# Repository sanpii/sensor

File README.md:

Temperature/humidity sensor over mqtt.

This is a part of [Uncontrolled Mechanical
Ventilation](https://hackaday.io/project/12708-uncontrolled-mechanical-ventilation)
project.

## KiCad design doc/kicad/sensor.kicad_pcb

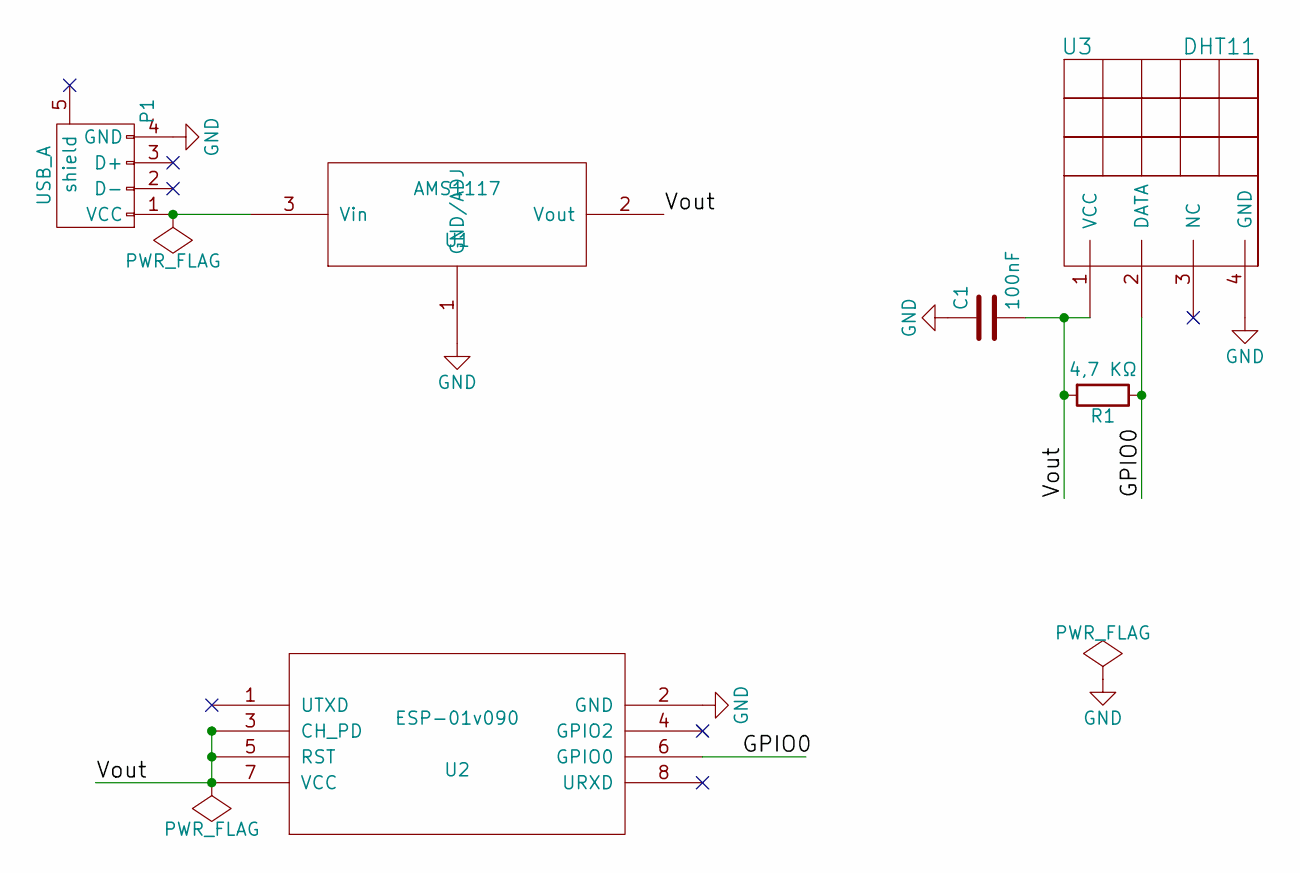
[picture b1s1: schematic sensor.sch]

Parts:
C1: 100nF; C_Disc_D3_P2.5
P1: USB_A
R1: 4,7 KΩ; Resistor_Cement_Horizontal_Meggitt-SBC-2
U1: AMS1117; Pin_Header_Straight_1x03
U2: ESP-01v090; ESP-01
U3: DHT11; Pin_Header_Straight_1x04

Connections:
/GPIO0: R1.1, U2.6 (GPIO0), U3.2 (DATA)
/Vout: C1.2, R1.2, U1.2 (Vout), U2.3 (CH_PD), U2.5 (RST), U2.7 (VCC), U3.1 (VCC)
GND: C1.1, P1.4 (GND), U1.1 (GND/ADJ), U2.2 (GND), U3.4 (GND)
unnamed: P1.1 (VCC), U1.3 (Vin)

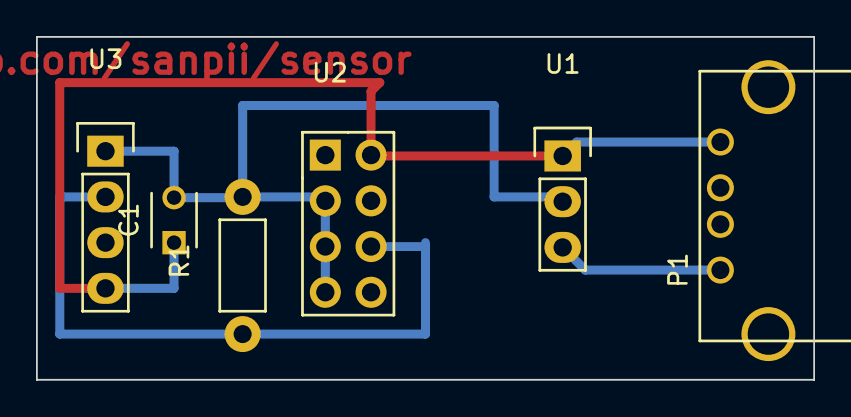
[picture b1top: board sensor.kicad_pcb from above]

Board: 2 copper layers, 43.2 x 19.1 mm, 6 parts (0 on the bottom side), 4 nets.

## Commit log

2016-07-19 Add sketch
2016-07-19 Add database structure
2016-07-26 Add license
2016-07-26 Add readme
2016-07-31 Add kicad project
2016-08-01 Create table if not exists
2016-08-04 Add link to project
2016-11-02 Add sql index
